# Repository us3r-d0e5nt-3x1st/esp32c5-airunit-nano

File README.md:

i think it's ready and it should work in the current state, but i still need to check if everything works in practice and write some kind of documentation for it. <br><br>
when you're downloading the files, please use either the main branch > code > download zip, or the project, photos and gerber zip files in the newest release, and not anything in the tags or the source code in the release, because they are older (broken) versions of the project

resources taken mostly from seeed's wiki for xiao s3 sense board + the amazing hx-esp32-cam-fpv project + the esp-cam schematic + the esp32-c5-wroom-1u datasheet + some weird random websites

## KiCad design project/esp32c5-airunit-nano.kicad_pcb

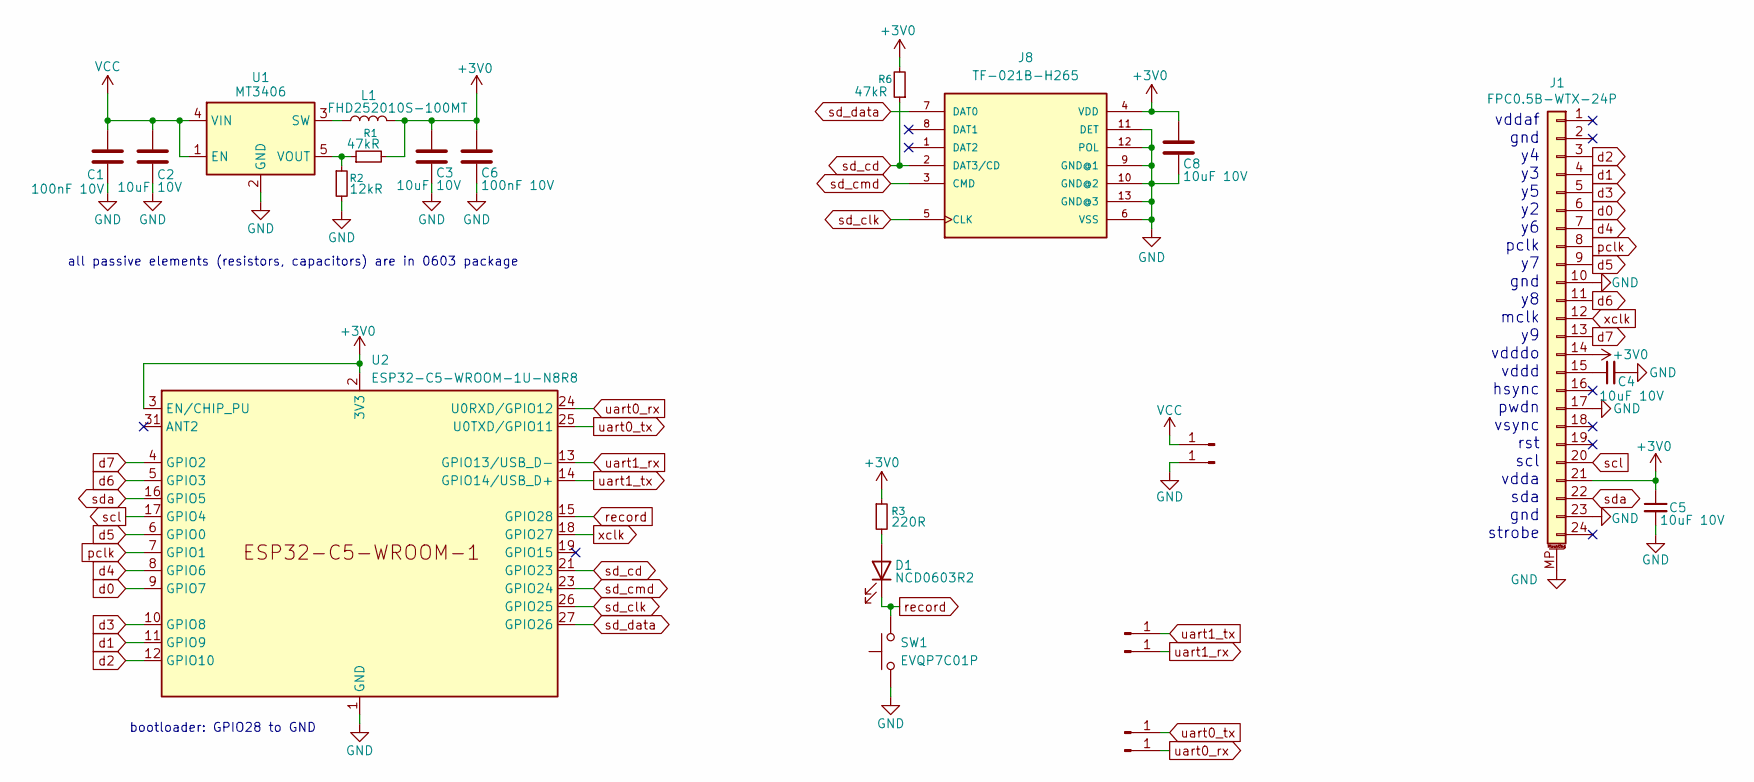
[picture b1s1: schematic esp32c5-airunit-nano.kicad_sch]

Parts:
C1, C6: 100nF 10V; C_0603_1608Metric
C2, C3, C4, C5, C8: 10uF 10V; C_0603_1608Metric
D1: NCD0603R2; LED_0603_1608Metric
J1: FPC0.5B-WTX-24P; TE_2-1734839-4_1x24-1MP_P0.5mm_Horizontal
J2, J4, J5, J6, J7, J9: Conn_01x01_Pin; SolderWirePad_1x01_SMD_2x3mm
J8: TF-021B-H265; MOLEX_0475710001
L1: FHD252010S-100MT; L_Changjiang_FNR252010S
R1, R6: 47kR; R_0603_1608Metric
R2: 12kR; R_0603_1608Metric
R3: 220R; R_0603_1608Metric
SW1: EVQP7C01P; SW_SPST_EVQP7C
U1: MT3406; TSOT-23-5
U2: ESP32-C5-WROOM-1U-N8R8; ESP32-C5-WROOM-1U

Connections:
+3V0: C3.1, C5.1, C6.1, C8.1, J1.14, J1.21, J8.4 (VDD), L1.2, R1.2, R3.1, R6.2, U2.2 (3V3), U2.3 (EN/CHIP_PU)
GND: C1.2, C2.2, C3.2, C4.2, C5.2, C6.2, C8.2, J1.10, J1.17, J1.23, J1.MP (MountPin), J4.1 (Pin_1_1), J8.6 (VSS), J8.9 (GND@1), J8.10 (GND@2), J8.11 (DET), J8.12 (POL), J8.13 (GND@3), R2.2, SW1.1, U1.2 (GND), U2.1 (GND), U2.28 (GND), U2.29 (GND), U2.30 (GND), U2.32 (GND)
unnamed: D1.2 (A), R3.2
unnamed: C4.1, J1.15
unnamed: L1.1, U1.3 (SW)
unnamed: R1.1, R2.1, U1.5 (VOUT)
VCC: C1.1, C2.1, J2.1 (Pin_1_1), U1.1 (EN), U1.4 (VIN)
d0: J1.6, U2.9 (GPIO7)
d1: J1.4, U2.11 (GPIO9)
d2: J1.3, U2.12 (GPIO10)
d3: J1.5, U2.10 (GPIO8)
d4: J1.7, U2.8 (GPIO6)
d5: J1.9, U2.6 (GPIO0)
d6: J1.11, U2.5 (GPIO3)
d7: J1.13, U2.4 (GPIO2)
pclk: J1.8, U2.7 (GPIO1)
record: D1.1 (K), SW1.2, U2.15 (GPIO28)
scl: J1.20, U2.17 (GPIO4)
sd_cd: J8.2 (DAT3/CD), R6.1, U2.21 (GPIO23)
sd_clk: J8.5 (CLK), U2.26 (GPIO25)
sd_cmd: J8.3 (CMD), U2.23 (GPIO24)
sd_data: J8.7 (DAT0), U2.27 (GPIO26)
sda: J1.22, U2.16 (GPIO5)
uart0_rx: J5.1 (Pin_1_1), U2.24 (U0RXD/GPIO12)
uart0_tx: J6.1 (Pin_1_1), U2.25 (U0TXD/GPIO11)
uart1_rx: J9.1 (Pin_1_1), U2.13 (GPIO13/USB_D-)
uart1_tx: J7.1 (Pin_1_1), U2.14 (GPIO14/USB_D+)
xclk: J1.12, U2.18 (GPIO27)

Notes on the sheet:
bootloader: GPIO28 to GND
all passive elements (resistors, capacitors) are in 0603 package
vddaf gnd y4 y3 y5 y2 y6 pclk y7 gnd y8 mclk y9 vdddo vddd hsync pwdn vsync rst scl vdda sda gnd strobe

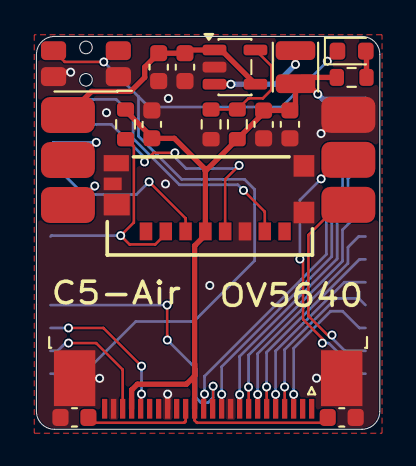
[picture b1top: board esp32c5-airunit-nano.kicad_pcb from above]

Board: 2 copper layers, 19.1 x 21.8 mm, 24 parts (1 on the bottom side), 28 nets.

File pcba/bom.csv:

"Reference","Qty","Value","Footprint","JLCPCB"
"C1,C6","2","100nF 50V","Capacitor_SMD:C_0603_1608Metric","C14663"
"C2,C3,C4,C5,C8","5","10uF 10V","Capacitor_SMD:C_0603_1608Metric","C19702"
"D1","1","RED","LED_SMD:LED_0603_1608Metric","C2286"
"J1","1","FPC0.5mm-24P","Connector_FFC-FPC:TE_2-1734839-4_1x24-1MP_P0.5mm_Horizontal","C5362165"
"J8","1","TF-021B-H265","0475710001:MOLEX_0475710001","C498185"
"L1","1","FHD252010S-100MT","Inductor_SMD:L_Changjiang_FNR252010S","C602007"
"R1,R6","2","47kR","Resistor_SMD:R_0603_1608Metric","C25600"
"R2","1","12kR","Resistor_SMD:R_0603_1608Metric","C22790"
"R3","1","220R","Resistor_SMD:R_0603_1608Metric","C1226"
"SW1","1","EVQP7C01P","Button_Switch_SMD:SW_SPST_EVQP7C","C388883"
"U1","1","MT3406","Package_TO_SOT_SMD:TSOT-23-5","C22462728"

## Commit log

2026-05-30 i've added some resources to help me create this project
2026-05-30 i've updated the readme file
2026-05-30 i've updated the readme file
    the link didn't go to the part of website i intended it to because of magic and quantum physics
2026-05-30 i've updated the readme
    cause the vision of the project changed
2026-05-30 i've added some VERY early project files
    tbh just some preparations for creating a project, not much more
2026-05-30 i've added a part of ov5640 datasheet and copied the airunit example description from the hx-esp32-cam-fpv project
2026-05-30 i've deleted this folder cause it's all in the /camera module files directory
2026-05-30 i've exchanged a copied file for a link
    because of the photos and pdfs
2026-05-30 i've updated the project files
    ! ! ! STILL UNFINISHED ! ! !
2026-06-01 i've updated the project files
    we're actually getting somewhere, the layout is pretty close to what i would call not bad
2026-06-05 i've uploaded the final project
2026-06-05 i've updated the schematic and changed the button for a cheaper one
2026-06-05 i've updated the readme file, now the project is ready
2026-06-05 the R2 should be 25kR
2026-06-05 i've added a note in the readme
    the R2 should be +/- 25kR, and not 22kR, we need 3.0V and not 3.3V
2026-06-05 i've fixed the R2 value everywhere
2026-06-05 i've updated the pcb screenshot in the readme
2026-06-07 i've updated the files
    there were some major errors in the v1.0 of the project
2026-06-07 i've updated the schematic in readme file
    it's actually v1.1, the bugfix, just forgot to change the version mark in the schematic
2026-06-08 i've uploaded the v1.2
2026-06-08 i've added the BOM and Pick&Place files needed for PCBA
2026-06-09 i've deleted the old c5-air-gerber.zip file that was left in the repo somewhere
